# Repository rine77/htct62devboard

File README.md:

# htct62devboard
A HT-CT62 dev board with breadboard compatibility
# pics

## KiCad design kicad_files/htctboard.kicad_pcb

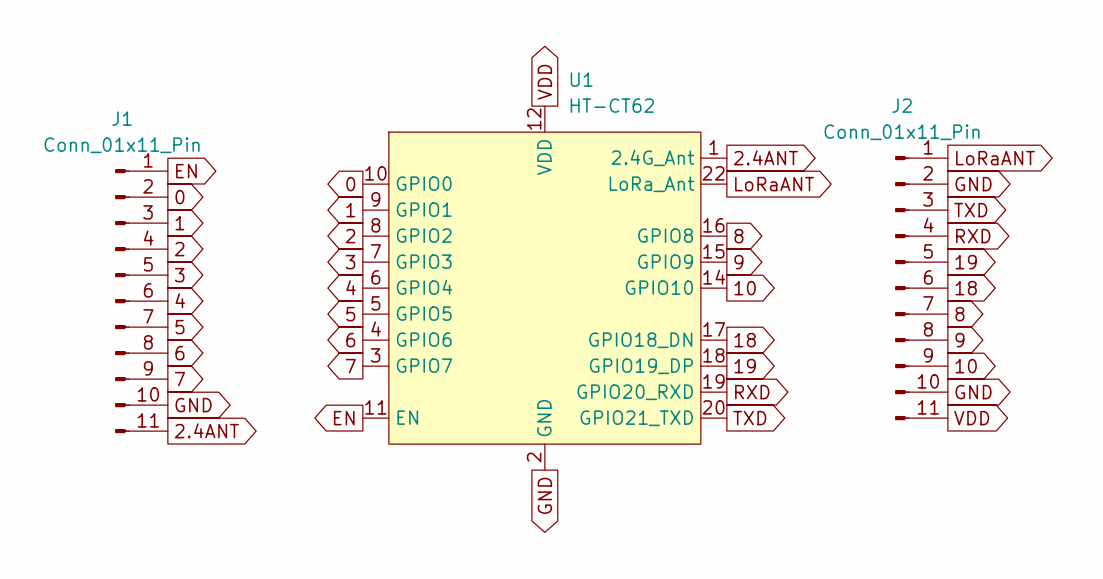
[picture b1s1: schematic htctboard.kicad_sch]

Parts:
J1, J2: Conn_01x11_Pin; PinHeader_1x11_P2.54mm_Vertical
U1: HT-CT62; Heltec_HT-CT62

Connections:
0: J1.2, U1.10 (GPIO0)
1: J1.3, U1.9 (GPIO1)
2: J1.4, U1.8 (GPIO2)
2.4ANT: J1.11, U1.1 (2.4G_Ant)
3: J1.5, U1.7 (GPIO3)
4: J1.6, U1.6 (GPIO4)
5: J1.7, U1.5 (GPIO5)
6: J1.8, U1.4 (GPIO6)
7: J1.9, U1.3 (GPIO7)
8: J2.7, U1.16 (GPIO8)
9: J2.8, U1.15 (GPIO9)
10: J2.9, U1.14 (GPIO10)
18: J2.6, U1.17 (GPIO18_DN)
19: J2.5, U1.18 (GPIO19_DP)
EN: J1.1, U1.11 (EN)
GND: J1.10, J2.2, J2.10, U1.2 (GND), U1.13 (GND), U1.21 (GND)
LoRaANT: J2.1, U1.22 (LoRa_Ant)
RXD: J2.4, U1.19 (GPIO20_RXD)
TXD: J2.3, U1.20 (GPIO21_TXD)
VDD: J2.11, U1.12 (VDD)

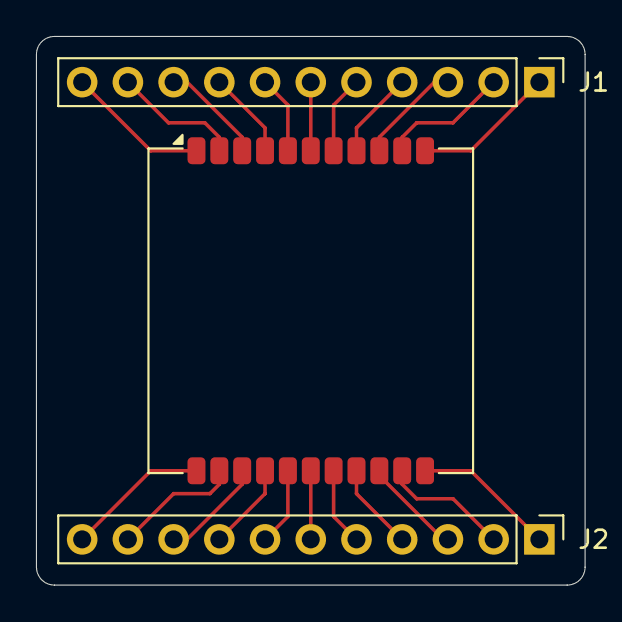
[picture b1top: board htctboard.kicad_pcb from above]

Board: 2 copper layers, 30.5 x 30.5 mm, 3 parts (0 on the bottom side), 20 nets.

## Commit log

2024-12-12 added pics
2024-12-12 added pictures with correct name
